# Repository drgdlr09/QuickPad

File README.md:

# QuickPad - A Brief Overview

fully assembled model

For Half-Life Week One, I designed QuickPad, a six-key macropad with a rotary encoder and 0.91" OLED screen. I designed QuickPad because my keyboard doesn't have any function keys, so I wanted to add some in the form of a macropad. During the design process, I also decided to add a rotary encoder for volume control. The OLED screen displays the date and time with the help of a DS3231 time module, which will keep track of time even when QuickPad is unplugged thanks to its coin cell battery.

Front of board

Back of board

# How it Works
QuickPad has:
- XIAO RP2040 microcontroller with 11 GPIO pins, all of which are used
- Six mechanical switches for function keys
- Rotary encoder for volume control
- 0.91" OLED screen for displaying date and time
- DS3231 clock module to keep time

QuickPad is built around the SEEED XIAO RP2040, a small microcontroller with 11 GPIO pins.

The switches use a direct pin layout, with each pin wired directly between a GPIO pin and ground. Switch 1 is mapped to pin D0, switch 2 is mapped to pin D1, switch 3 is mapped to pin D2, switch 4 is mapped to pin D3, switch 5 is mapped to D8, and switch 6 is mapped to D9. The firmware matches each switches 1-6 to F1-F6 respectively. When a key is pressed, the firmware sends the HID code for that key, thus triggering the response.

The rotary encoder is what controls volume. Turning clockwise turns the volume up and turning counterclockwise turns the volume down. Pressing the rotary encoder mutes the volume. Similarly to the switches, each input sends an HID code to get a response that triggers volume up/down or mute. The encoder's A pin is on D6, the B pin is on D7, and S1 is on D10.

The OLED Display and clock module work hand-in-hand. The display displays the current time and the clock module keeps track of time, even when QuickPad is unplugged. As soon as the firmware is compiled, the time is set and saved. This is a great feature for when I need to unplug the macropad to plug in other devices, like my phone or desk lamp. Both components use D4 and D5 for SDA and SCL capabilities.

*NOTE: Based on what I saw, although it looks like the microcontroller collides with switch 2 in the PCB layout, it shouldn't because the microcontroller is on the back of the board, not the front, so there shouldn't be any collisions (See 3D rendering above to confirm please; I could be wrong).

# The Case
The case has a similar design to my actual keyboard. It is comprised of 3 main parts: the main body, the top enclosure, and the rotary encoder knob. The main body has a sleep angular design with rounded edges for ergonomics when it needed to be moved. It also has a small hole for the USB port. The PCB is slightly raised to make room for the bottom components and also to create an inclined angled of typing.

The top enclosure has 3 cutouts: one for the keys, one for the rotary encoder, and one for the OLED screen. The one for the OLED screen has a small enclosure around it to stabilize the screen and keep it flush against the top enclosure. If the included pins do not reach the OLED screen, I will cut wires to the size needed to attach the screen to the board. The enclosure has a very tight fit so it can easily snap in place without the need of screws.

Finally, the rotary encoder knob has a filleted top edge for ergonomics. it is 10mm tall and 12mm wide. I was intending to add a textured surface, but I had trouble adding it so I left it smooth.

# Bill of Materials

| Part | Quantity | Unit Price | Total | Vendor |
| --- | --- | --- | --- | --- |
| XIAO RP2040 | 1 | 3.99 | 3.99 | Seeed |
| Keycaps | 24 | 0.37 | 8.88 | Amazon |
| PCB | 5 | 0.23 | 1.15 | JLCPCB |
| 0.91" OLED Screen | 2 | 4.00 | 8.00 | Amazon |
| DS3231 | 2 | 4.00 | 8.00 | Amazon |

TOTAL PRICE (INCLUDING $2.22 SHIPPING/TAX): $28.25

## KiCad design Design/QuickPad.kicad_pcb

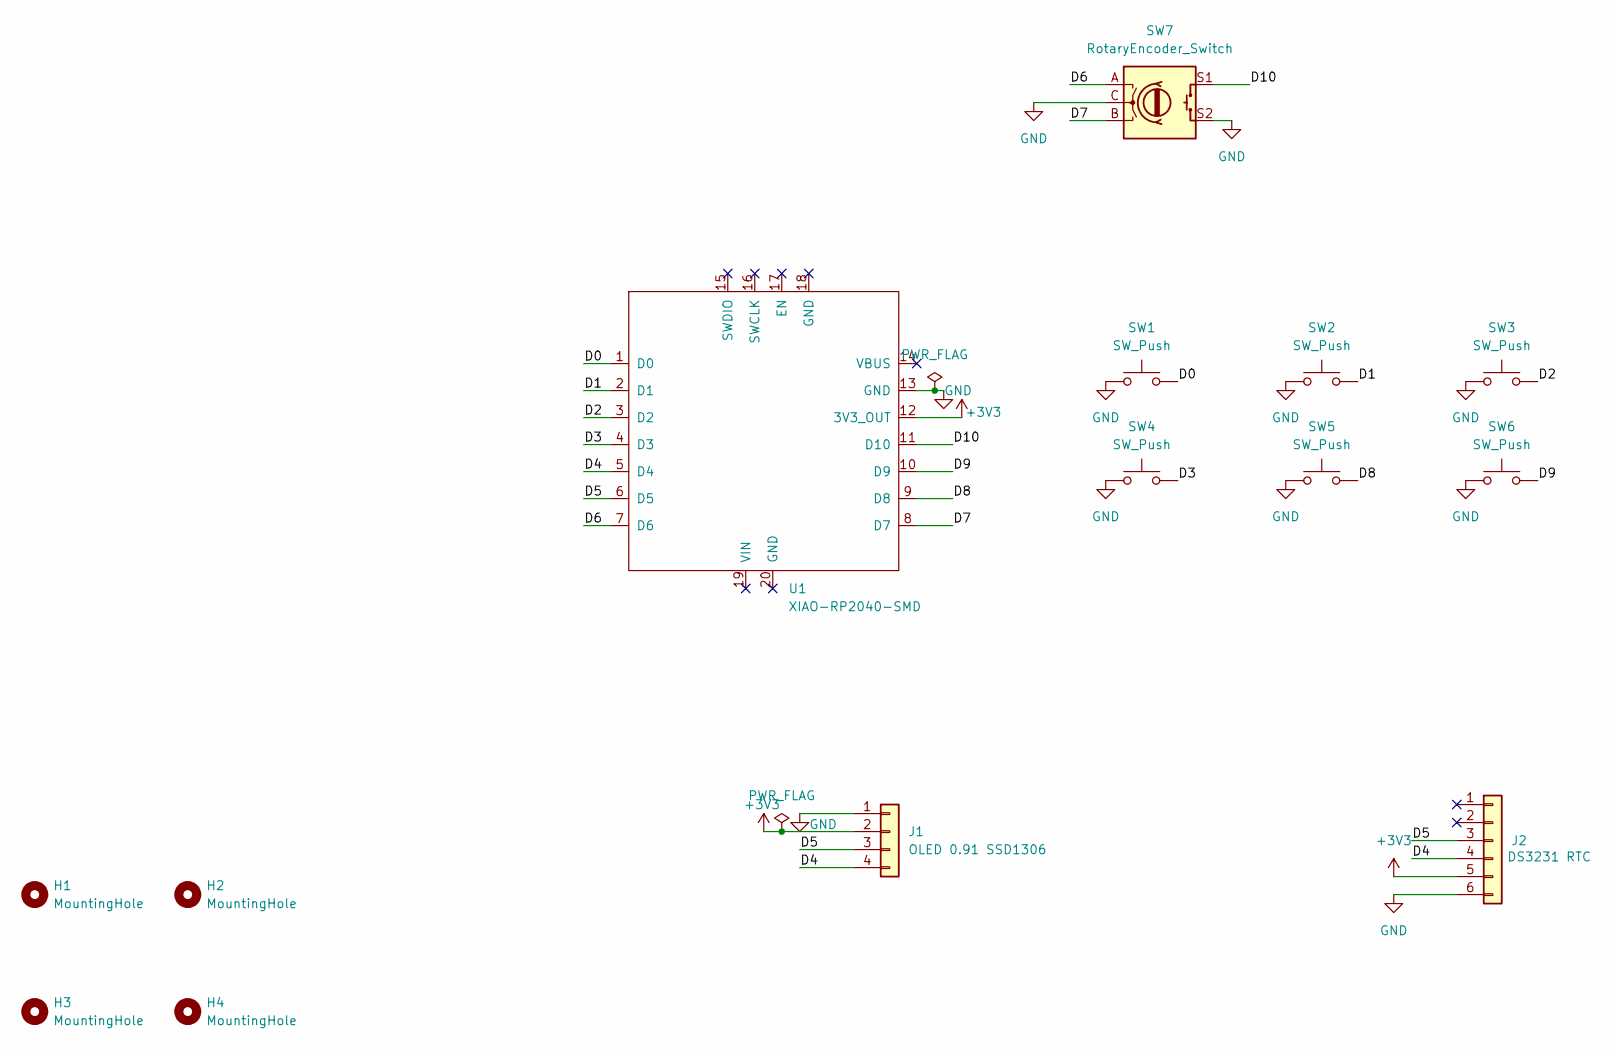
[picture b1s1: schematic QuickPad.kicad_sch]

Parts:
H1, H2, H3, H4: MountingHole; MountingHole_2.7mm_M2.5
J1: OLED 0.91 SSD1306; PinHeader_1x04_P2.54mm_Vertical
J2: DS3231 RTC; PinHeader_1x06_P2.54mm_Vertical
SW1, SW2, SW3, SW4, SW5, SW6: SW_Push; SW_Cherry_MX_1.00u_PCB
SW7: RotaryEncoder_Switch; RotaryEncoder_Alps_EC11E-Switch_Vertical_H20mm
U1: XIAO-RP2040-SMD

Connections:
+3V3: J1.2, J2.5, U1.12 (3V3_OUT)
/D0: SW1.2, U1.1 (D0)
/D1: SW2.2, U1.2 (D1)
/D2: SW3.2, U1.3 (D2)
/D3: SW4.2, U1.4 (D3)
/D4: J1.4, J2.4, U1.5 (D4)
/D5: J1.3, J2.3, U1.6 (D5)
/D6: SW7.A, U1.7 (D6)
/D7: SW7.B, U1.8 (D7)
/D8: SW5.2, U1.9 (D8)
/D9: SW6.2, U1.10 (D9)
/D10: SW7.S1, U1.11 (D10)
GND: J1.1, J2.6, SW1.1, SW2.1, SW3.1, SW4.1, SW5.1, SW6.1, SW7.C, SW7.S2, U1.13 (GND)

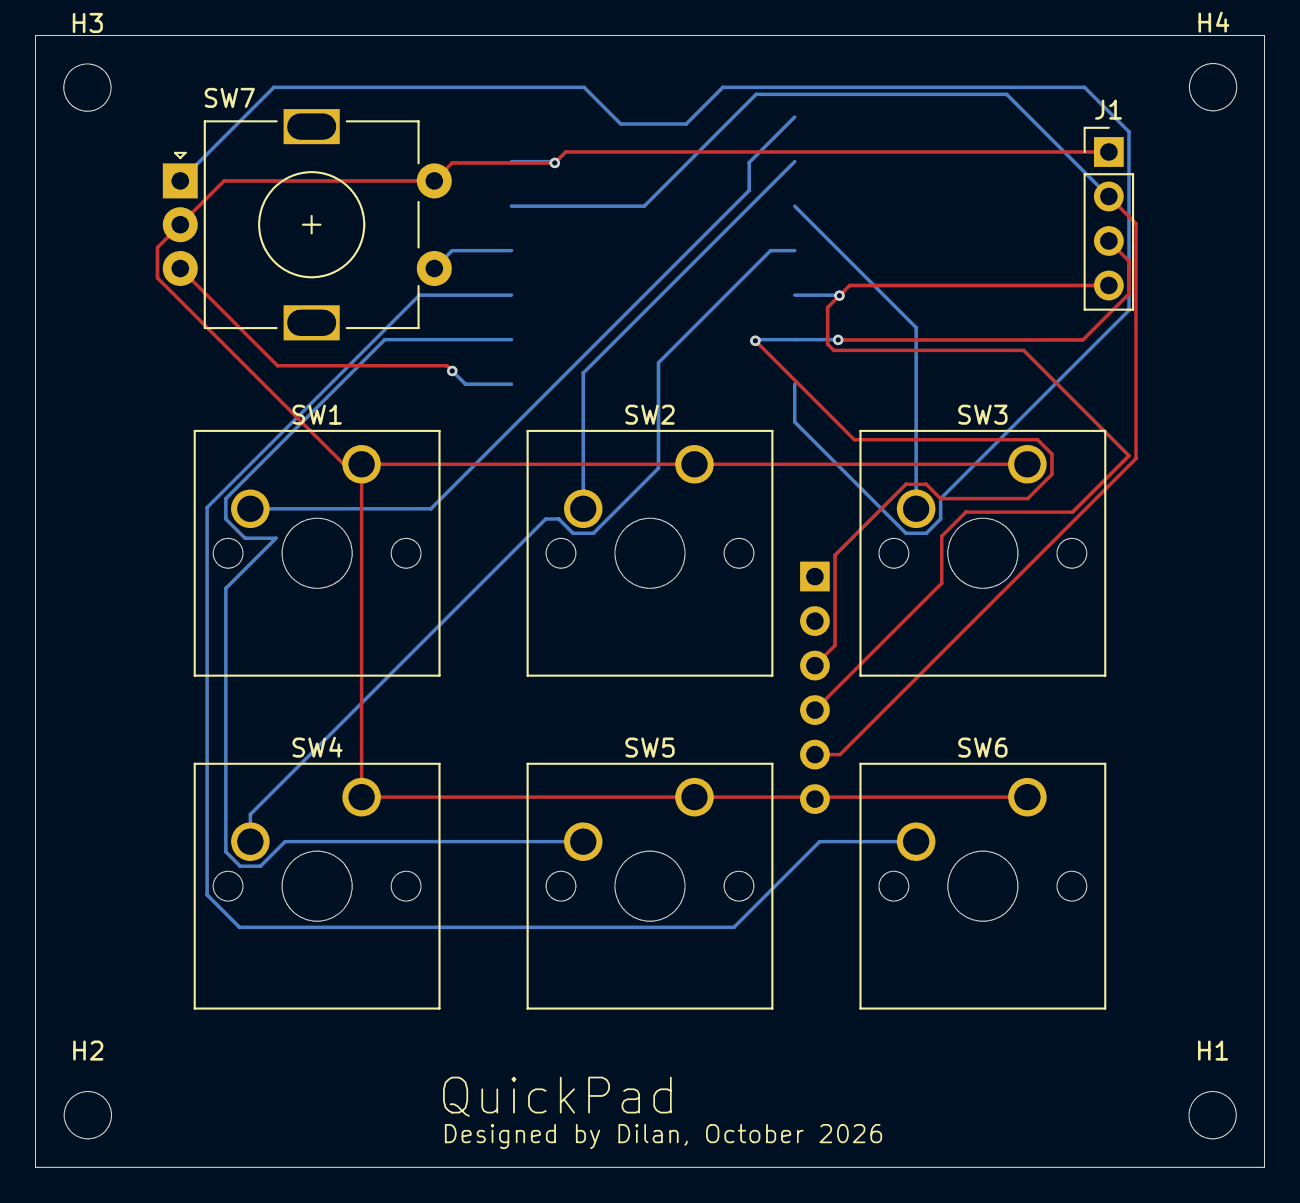
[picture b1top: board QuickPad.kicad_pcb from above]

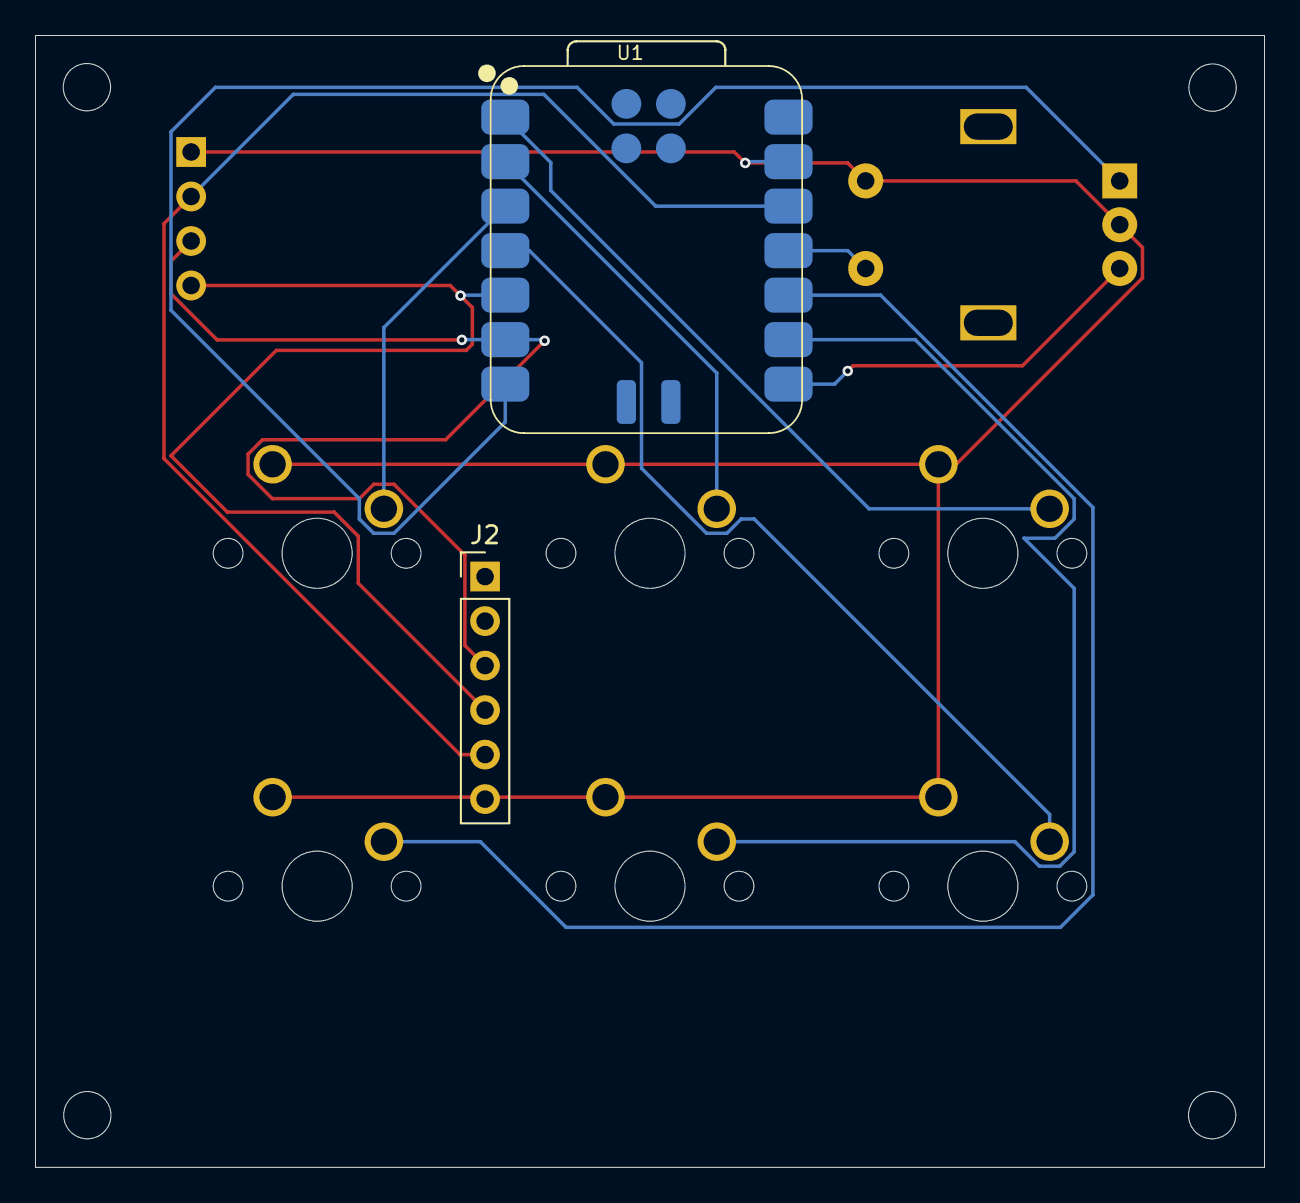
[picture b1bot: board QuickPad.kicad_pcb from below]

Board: 2 copper layers, 70.1 x 64.6 mm, 14 parts (2 on the bottom side), 13 nets.

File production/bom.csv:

Designator,Footprint,Quantity,Value,LCSC Part #
J1,PinHeader_1x04_P2.54mm_Vertical,1,OLED 0.91 SSD1306,
J2,PinHeader_1x06_P2.54mm_Vertical,1,DS3231 RTC,
"SW1, SW2, SW3, SW4, SW5, SW6",SW_Cherry_MX_1.00u_PCB,6,SW_Push,
SW7,RotaryEncoder_Alps_EC11E-Switch_Vertical_H20mm,1,RotaryEncoder_Switch,
U1,XIAO-RP2040-SMD,1,XIAO-RP2040-SMD,
